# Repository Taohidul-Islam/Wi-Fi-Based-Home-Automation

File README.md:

# Wi-Fi-Based-Home-Automation
<h2>This Board can turn any regular household electric switchboard into a smart Wi-Fi and Remote controlled switchboard.</h2>
<p>Here the board I designed is fail protected, meaning even if my electronic logic fails, the switchboard would work like a regular switchboard. The Automation Board is designed maintaining hierarchy. Meaning the Automation Board can only work only if the main switch from switch board is set to "on". In my logic I don't really turn anything "On". Everything is default "On" and "Off" by switchboard. I can just turn the things "Off" when the switch is "On" by triggering relay and turn the things back to it's default "On" position</p>
<p>N.B. IR remote control is currently unavailable and AC induction fan control channel can be faulty as it is not tested(will test soon).</p>

<P>Here are some screenshots of my PCB And Schematics</P>

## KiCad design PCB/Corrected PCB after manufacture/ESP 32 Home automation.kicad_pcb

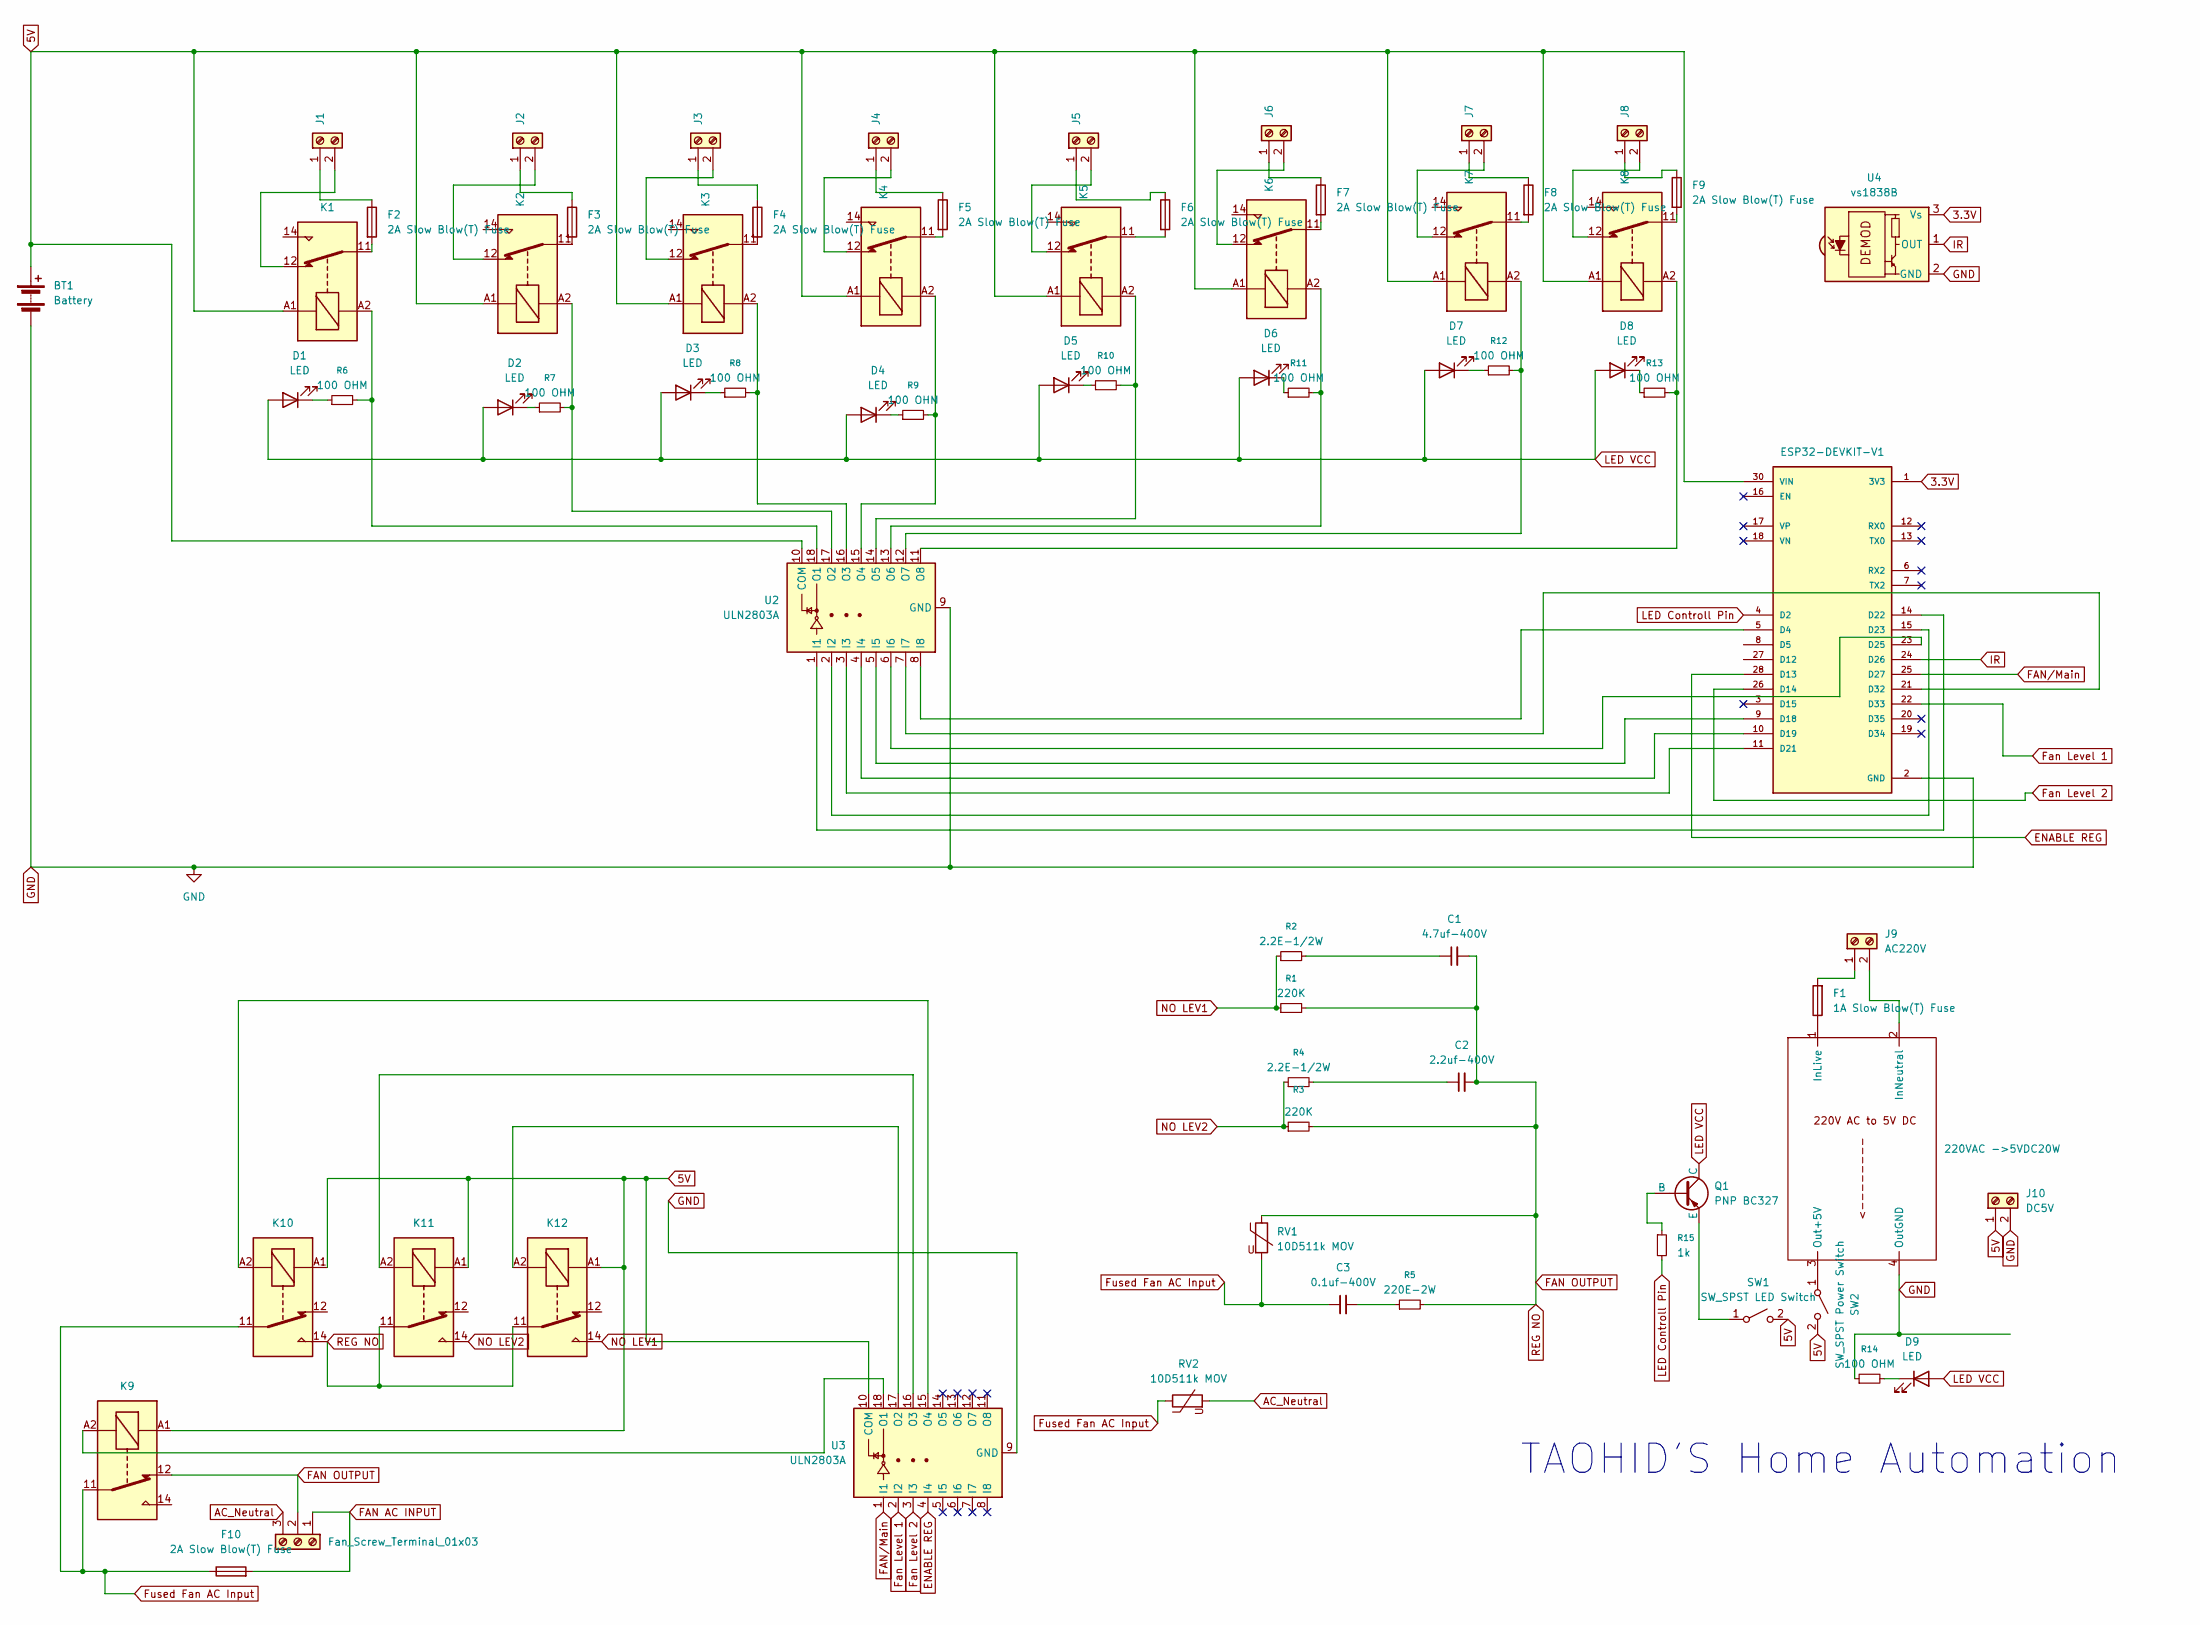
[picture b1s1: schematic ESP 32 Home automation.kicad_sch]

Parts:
Adapter/Charger1: 220VAC ->5VDC20W; ACtoDC power Adapter. 220V to 5V
BT1: Battery; TerminalBlock_MaiXu_MX126-5.0-02P_1x02_P5.00mm
C1: 4.7uf-400V; C_Rect_L32.0mm_W15.0mm_P27.00mm
C2: 2.2uf-400V; C_Rect_L27.0mm_W9.0mm_P22.00mm
C3: 0.1uf-400V; C_Rect_L13.0mm_W6.5mm_P7.50mm_P10.00mm
D1, D2, D3, D4, D5, D6, D7, D8, D9: LED; LED_D5.0mm
F1: 1A Slow Blow(T) Fuse; Fuseholder_Littelfuse_100_series_5x20mm
F2, F3, F4, F5, F6, F7, F8, F9, F10: 2A Slow Blow(T) Fuse; Fuseholder_Littelfuse_100_series_5x20mm
J1, J2, J3, J4, J5, J6, J7, J8: Screw_Terminal_01x02; TerminalBlock_Phoenix_MKDS-1,5-2-5.08_1x02_P5.08mm_Horizont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
J9: AC220V; TerminalBlock_Phoenix_MKDS-1,5-2-5.08_1x02_P5.08mm_Horizont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
J10: DC5V; TerminalBlock_Phoenix_MKDS-1,5-2-5.08_1x02_P5.08mm_Horizont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
J11: Fan_Screw_Terminal_01x03; TerminalBlock_Phoenix_MKDS-1,5-3-5.08_1x03_P5.08mm_Horizont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
K1, K2, K3, K4, K5, K6, K7, K8, K9, K10, K11, K12: JQC-3FF-005-1Z; Relay_SPDT_Hongfa_JQC-3FF_0XX-1Z
Q1: PNP BC327; TO-92_Inline
R1, R3: 220K; R_Axial_DIN0309_L9.0mm_D3.2mm_P20.32mm_Horizontal
R2, R4: 2.2E-1/2W; R_Axial_DIN0309_L9.0mm_D3.2mm_P20.32mm_Horizontal
R5: 220E-2W; R_Axial_DIN0309_L9.0mm_D3.2mm_P20.32mm_Horizontal
R6, R7, R8, R9, R10, R11, R12, R13, R14: 100 OHM; R_Axial_DIN0207_L6.3mm_D2.5mm_P7.62mm_Horizontal
R15: 1k; R_Axial_DIN0207_L6.3mm_D2.5mm_P7.62mm_Horizontal
RV1, RV2: 10D511k MOV; RV_Disc_D12mm_W7.5mm_P7.5mm
SW1: SW_SPST LED Switch; TerminalBlock_Phoenix_MKDS-1,5-2_1x02_P5.00mm_Horizontal
SW2: SW_SPST Power Switch; TerminalBlock_Phoenix_MKDS-1,5-2_1x02_P5.00mm_Horizontal
U1: ESP32-DEVKIT-V1; MODULE_ESP32_DEVKIT_V1; PARTREV N/A
U2, U3: ULN2803A; DIP-18_W7.62mm_Socket_LongPads
U4: vs1838B; Vishay_MOLD-3Pin

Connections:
3.3V: U1.1 (3V3), U4.3 (Vs)
5V: BT1.1 (+), J10.1, K1.A1, K2.A1, K3.A1, K4.A1, K5.A1, K6.A1, K7.A1, K8.A1, K9.A1, K10.A1, K11.A1, K12.A1, SW1.2 (B), SW2.2 (B), U1.30 (VIN), U2.10 (COM), U3.10 (COM)
AC_Neutral: J11.3, RV2.2; also elsewhere on the board
ENABLE REG: U1.28 (D13), U3.4 (I4)
FAN AC INPUT: F10.2, J11.1
FAN/Main: U1.25 (D27), U3.1 (I1)
Fan Level 1: U1.22 (D33), U3.2 (I2)
Fan Level 2: U1.26 (D14), U3.3 (I3)
Fused Fan AC Input: C3.1, F10.1, K9.11, K10.11, RV1.2, RV2.1
GND: Adapter/Charger1.4 (OutGND), BT1.2 (-), J10.2, R14.1, U1.2 (GND), U1.29 (GND), U2.9 (GND), U3.9 (GND), U4.2 (GND)
IR: U1.24 (D26), U4.1 (OUT)
LED Controll Pin: R15.2, U1.4 (D2)
LED VCC: D1.2 (A), D2.2 (A), D3.2 (A), D4.2 (A), D5.2 (A), D6.2 (A), D7.2 (A), D8.2 (A), D9.2 (A), Q1.1 (C)
NO LEV1: K12.14, R1.1, R2.1
NO LEV2: K11.14, R3.1, R4.1
unnamed: Adapter/Charger1.1 (InLive), F1.1
unnamed: Adapter/Charger1.2 (InNeutral), J9.2
unnamed: Adapter/Charger1.3 (Out+5V), SW2.1 (A)
unnamed: C1.1, R2.2
unnamed: C2.1, R4.2
unnamed: C3.2, R5.1
unnamed: D2.1 (K), R7.1
unnamed: D3.1 (K), R8.1
unnamed: D4.1 (K), R9.1
unnamed: D5.1 (K), R10.1
unnamed: D6.1 (K), R11.1
unnamed: D7.1 (K), R12.1
unnamed: D8.1 (K), R13.1
unnamed: D9.1 (K), R14.2
unnamed: F2.2, K1.11
unnamed: F3.2, K2.11
unnamed: F4.2, K3.11
unnamed: F5.2, K4.11
unnamed: F6.2, K5.11
unnamed: F7.2, K6.11
unnamed: F8.2, K7.11
unnamed: F9.2, K8.11
unnamed: F2.1, J1.1
unnamed: J1.2, K1.12
unnamed: F3.1, J2.1
unnamed: J2.2, K2.12
unnamed: F4.1, J3.1
unnamed: J3.2, K3.12
unnamed: F5.1, J4.1
unnamed: J4.2, K4.12
unnamed: F6.1, J5.1
unnamed: J5.2, K5.12
unnamed: F7.1, J6.1
unnamed: J6.2, K6.12
unnamed: F8.1, J7.1
unnamed: J7.2, K7.12
unnamed: F9.1, J8.1
unnamed: J8.2, K8.12
unnamed: F1.2, J9.1
unnamed: Q1.2 (B), R15.1
unnamed: Q1.3 (E), SW1.1 (A)
unnamed: U1.5 (D4), U2.8 (I8)
unnamed: U1.9 (D18), U2.5 (I5)
unnamed: U1.10 (D19), U2.4 (I4)
unnamed: U1.11 (D21), U2.3 (I3)
unnamed: U1.14 (D22), U2.1 (I1)
unnamed: U1.15 (D23), U2.2 (I2)
unnamed: U1.23 (D25), U2.6 (I6)
unnamed: U1.21 (D32), U2.7 (I7)
unnamed: K2.A2, R7.2, U2.17 (O2)
unnamed: K3.A2, R8.2, U2.16 (O3)
unnamed: K4.A2, R9.2, U2.15 (O4)
unnamed: K5.A2, R10.2, U2.14 (O5)
unnamed: K6.A2, R11.2, U2.13 (O6)
unnamed: K7.A2, R12.2, U2.12 (O7)
unnamed: K8.A2, R13.2, U2.11 (O8)
unnamed: K9.A2, U3.18 (O1)
unnamed: K12.A2, U3.17 (O2)
unnamed: K11.A2, U3.16 (O3)
unnamed: K10.A2, U3.15 (O4)

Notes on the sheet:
TAOHID'S Home Automation

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
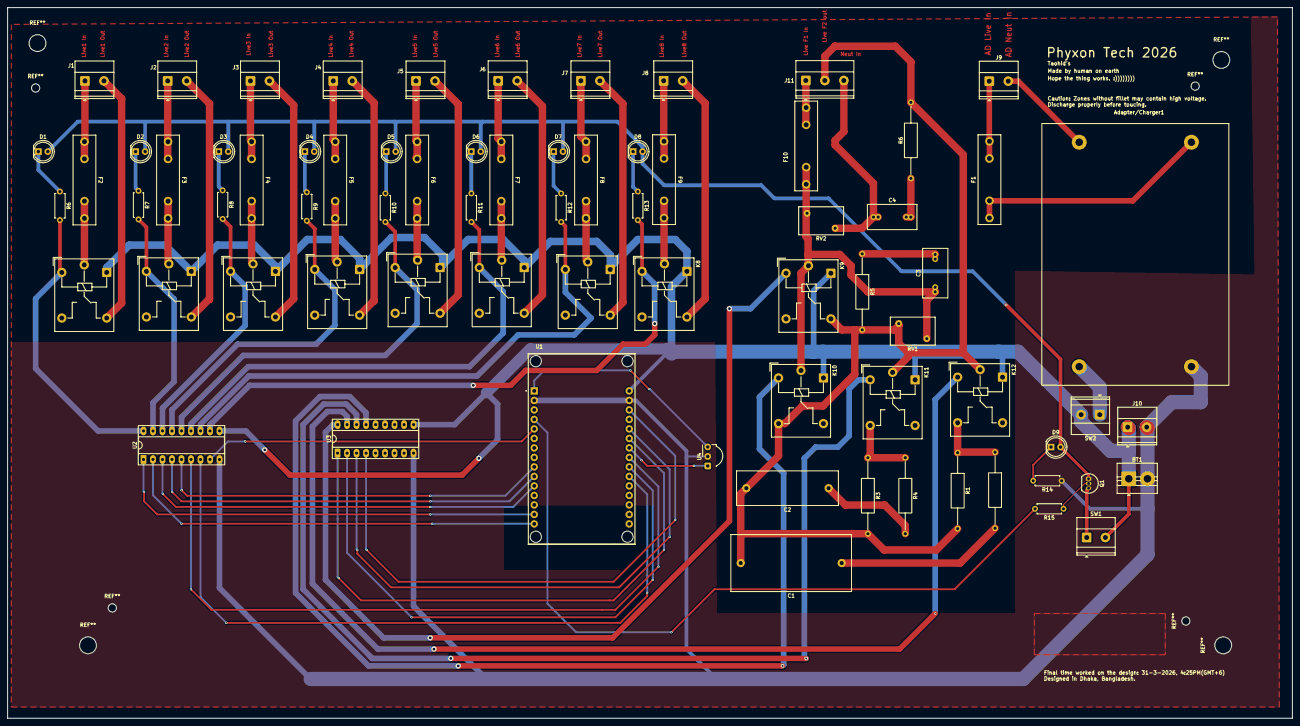
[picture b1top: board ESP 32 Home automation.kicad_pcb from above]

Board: 2 copper layers, 343.5 x 190.0 mm, 73 parts (0 on the bottom side), 79 nets.

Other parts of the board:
C4: 0.1uf-400V; C_Rect_L13.0mm_W6.5mm_P7.50mm_P10.00mm
R6#2: 100 OHM; R_Axial_DIN0207_L6.3mm_D2.5mm_P7.62mm_Horizontal

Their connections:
AC_Neutral: C4.1; also elsewhere on the board

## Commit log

2025-12-23 Enhance README with project details and images
    Added detailed description and images for the ESP-32 home automation project.
2025-12-23 Add LICENSE file with copyright information
    Added license file with copyright and usage terms.
2025-12-24 Add new Temp file with initial content
2025-12-24 Update BOM.csv with new product entries
2025-12-24 Update JOURNAL.md with project progress details
    Documented progress on project PCB, including research on TRIAC control, schematic modifications for safety, PCB design, routing completion, and coding.
2025-12-24 Fix formatting of time spent in JOURNAL.md
2026-02-02 Add initial content to temp file
2026-02-02 Add additional screenshots to README
    Added new screenshots to the README for better visual representation.
2026-02-02 Rename project from ESP-32 to Wi-Fi-Based Home Automation
2026-02-02 Rename HOME AUTOMATION CASE NO LID.step to HOME AUTOMATION CASE DISASSEMBLED NO LID.step
2026-02-03 Create temp
2026-03-10 Create 3D Model
2026-03-10 Document case modifications and PCB standoffs
    Added details about adding standoffs to the case for PCB security.
2026-06-09 Creating firmware V2.6
2026-06-09 Add HTTP server for firmware updates
